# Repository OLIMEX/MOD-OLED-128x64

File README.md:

# MOD-OLED-128x64
MOD-OLED-128x64 is low power OLED display module with UEXT connector.

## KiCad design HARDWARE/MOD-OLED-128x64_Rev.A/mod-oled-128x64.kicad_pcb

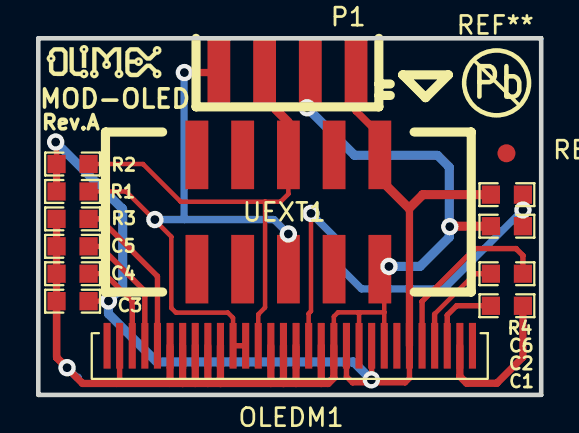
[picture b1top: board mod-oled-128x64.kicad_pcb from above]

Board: 2 copper layers, 27.9 x 19.8 mm, 13 parts (0 on the bottom side), 12 nets.

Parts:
C1, C2, C3: 105; C_0603
C4: 225; C_0603
C5: 106; C_0603
C6: 104; C_0603
OLEDM1: IROP055; IROP055-SSD1306Z-PADS-ONLY
P1: CONN_01X04; SIP4_SMD
R1, R2, R4: 103; R_0603
R3: 394; R_0603
UEXT1: CONN_02X05; UEXTM-SMD

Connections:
/SCL: OLEDM1.18, P1.3, R2.2, UEXT1.5
/SDA: OLEDM1.19, OLEDM1.20, P1.4, R1.2, UEXT1.6
/VDD: C3.1, OLEDM1.6, OLEDM1.9, OLEDM1.11, P1.1, R1.1, R2.1, R4.1, UEXT1.1
GND: C3.2, C4.2, C5.2, C6.1, OLEDM1.8, OLEDM1.10, OLEDM1.12, OLEDM1.13, OLEDM1.15, OLEDM1.16, OLEDM1.17, OLEDM1.21, OLEDM1.22, OLEDM1.23, OLEDM1.24, OLEDM1.25, OLEDM1.29, P1.2, R3.2, UEXT1.2
unnamed: C1.1, OLEDM1.2
unnamed: C1.2, OLEDM1.3
unnamed: C2.1, OLEDM1.4
unnamed: C2.2, OLEDM1.5
unnamed: C4.1, OLEDM1.28
unnamed: C5.1, OLEDM1.27
unnamed: C6.2, OLEDM1.14, R4.2
unnamed: OLEDM1.26, R3.1

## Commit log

2015-07-01 update CAD and software files
2015-07-01 schematic in PDF format
2015-07-01 Added pyMOD-OLED submodule
2018-05-24 All GND symbols should point down
